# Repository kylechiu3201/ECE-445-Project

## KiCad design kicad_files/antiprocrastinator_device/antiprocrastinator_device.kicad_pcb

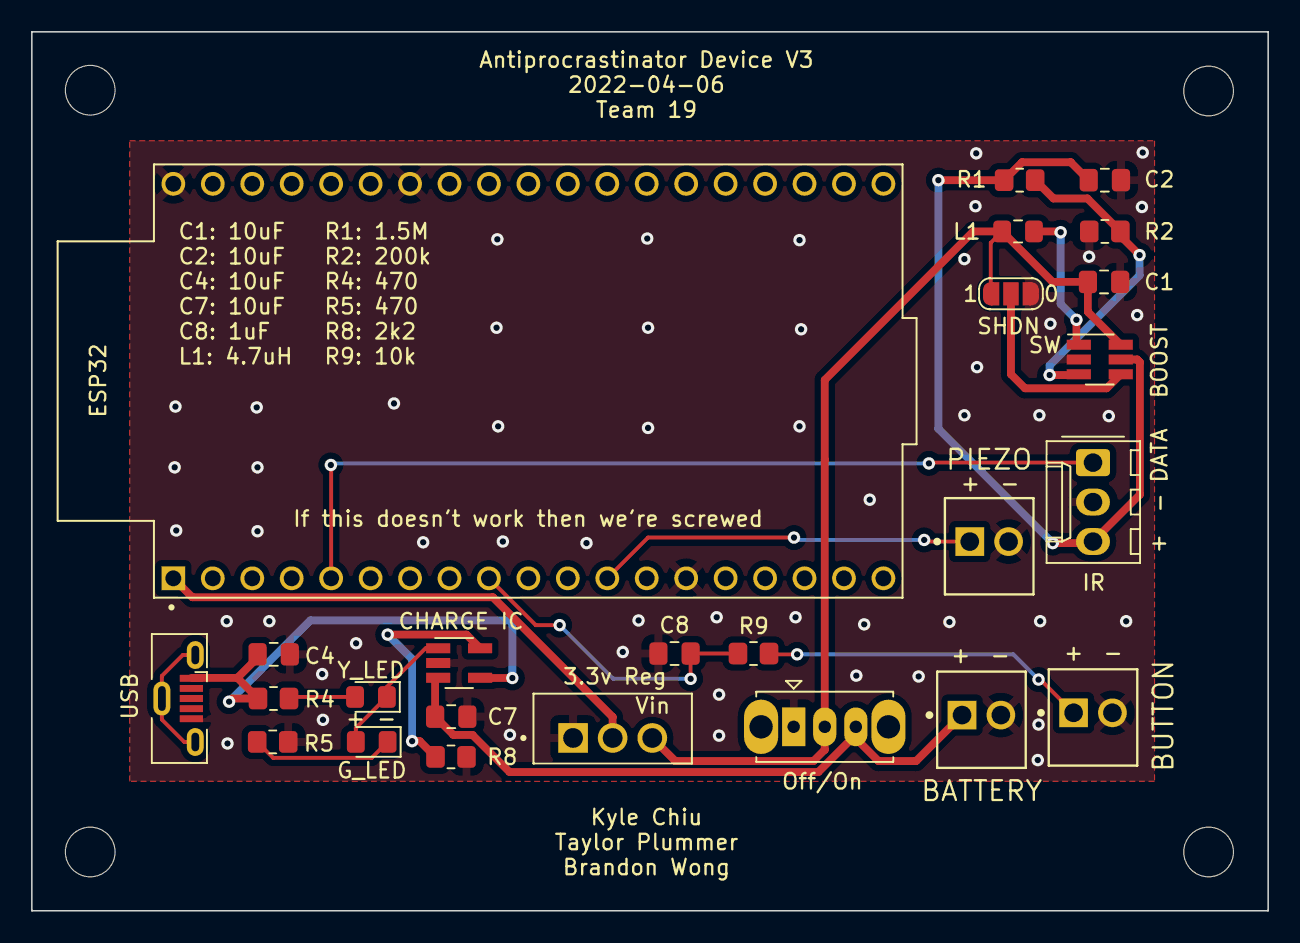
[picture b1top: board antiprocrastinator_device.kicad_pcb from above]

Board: 2 copper layers, 79.6 x 56.6 mm, 29 parts (0 on the bottom side), 17 nets.

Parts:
3.3v Reg: 3.3v-Reg; TO255P1020X450X1968-3
BOOST: Boost Converter; SOT-23-6_Handsoldering
C1, C2, C4, C7: 10uF; C_0805_2012Metric_Pad1.18x1.45mm_HandSolder
C8: 1uF; C_0805_2012Metric_Pad1.18x1.45mm_HandSolder
CHARGE IC: BATT_IC; SOT-23-5_HandSoldering
D2: Y_LED; LED_0805_2012Metric_Pad1.15x1.40mm_HandSolder
D3: G_LED; LED_0805_2012Metric_Pad1.15x1.40mm_HandSolder
ESP32: ESP32; MODULE_ESP32-DEVKITC-32U
H1, H2, H3, H4: MountingHole; MountingHole_3.2mm_M3
J5: PIEZO; Molex-22-04-1021-MFG
J6: BATTERY; Molex-22-04-1021-MFG
J7: BUTTON; Molex-22-04-1021-MFG
J9: IR; Molex_KK-254_AE-6410-03A_1x03_P2.54mm_Vertical
L1: 4.7uH; L_0805_2012Metric_Pad1.15x1.40mm_HandSolder
Off/On: SW_SPDT; SW_Slide_1P2T_CK_OS102011MS2Q
R1: 1.5M; R_0805_2012Metric_Pad1.20x1.40mm_HandSolder
R2: 200k; R_0805_2012Metric_Pad1.20x1.40mm_HandSolder
R4, R5: 470R; R_0805_2012Metric_Pad1.20x1.40mm_HandSolder
R8: 2K2; R_0805_2012Metric_Pad1.20x1.40mm_HandSolder
R9: 10k; R_0805_2012Metric_Pad1.20x1.40mm_HandSolder
SHDN: SolderJumper_3_Open; SolderJumper-3_P1.3mm_Open_RoundedPad1.0x1.5mm_NumberLabels
USB: USB_B_Micro; USB_Micro-B_Molex-105133-0001

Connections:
+3V3: 3.3v Reg.2 (VOUT), ESP32.1 (3V3)
/BATT_OUT: 3.3v Reg.3 (VIN), BOOST.6 (VIN), C1.1, L1.1, Off/On.2 (B), SHDN.1 (A)
/BOOST_FB: BOOST.3 (FB), R1.2, R2.1
/BOOST_SHDN: BOOST.4 (~SHDN), SHDN.2 (C)
/BOOST_SW: BOOST.1 (SW), L1.2
/BOOST_VOUT: BOOST.5 (VOUT), C2.1, J9.3, R1.1
/BUTTON: C8.1, ESP32.9 (IO25), R9.2
/IR_DATA: ESP32.5 (IO34), J9.1
/PIEZO: ESP32.12 (IO14), J5.1
GND: 3.3v Reg.1 (ADJ/GND), BOOST.2 (GND), C1.2, C2.2, C4.2, C7.2, C8.2, CHARGE IC.2 (VSS), ESP32.14 (GND1), ESP32.32 (GND2), ESP32.38 (GND3), J5.2, J6.2, J7.2, J9.2, Off/On.1 (A), R2.2, R5.2, R8.2, SHDN.3 (B), USB.5 (GND)
unnamed: C4.1, CHARGE IC.4 (VDD), R4.1, USB.1 (VBUS)
unnamed: C7.1, CHARGE IC.3 (VBAT), J6.1, Off/On.3 (C)
unnamed: CHARGE IC.1 (STAT), D2.1 (K), D3.2 (A)
unnamed: D2.2 (A), R4.2
unnamed: D3.1 (K), R5.1
unnamed: J7.1, R9.1
unnamed: CHARGE IC.5 (PROG), R8.1

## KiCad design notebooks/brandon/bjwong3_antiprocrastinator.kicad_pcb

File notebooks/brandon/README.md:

## __2/22/2022__
Worked on the first draft of the pcb in KiCad, adding and connecting all the components within the schematic. The piezo buzzer, bluetooth module, and DIP sockets were not within the standard library of footprints and symbols that KiCad provides. For the piezo buzzer, I represented it as a generic buzzer for reference while importing the DIP sockets and bluetooth module from [KiCad Libraries](https://kicad.github.io/footprints/Package_DIP) and [SnapEDA](https://www.snapeda.com/parts/HC-05/ITead%20Studio/view-part/?company=N%2FA&amp;). The schematic is roughly based on the block diagram and will most likely need revisions given more research.

## __2/24/2022__
Finished Design Document. Added more specifics regarding the control subsystem based on TA suggestion. The device will now check for running websites/programs every 5 seconds, and sends the square wave to the buzzer if it detects a blacklisted item. It will run on a 3 minute-interval of sending the signal and not sending the signal should the blacklisted item continue to run.

## __2/28/2022__
Finished the first draft of the pcb board in KiCad. After doing more research on the parts we plan to use as well as importing their models from SnapEDA ([Battery Connector](https://www.snapeda.com/parts/B2B-XH-A(LF)(SN)/JST%20Sales%20America%20Inc./view-part/), [Voltage Regulator](https://www.snapeda.com/parts/LD1117V33/STMicroelectronics/view-part/), [Switch](https://www.snapeda.com/parts/EG1218/E-Switch/view-part/)), I completed a more accurate schematic of what our potentially board will look like. This allowed me to arrange and route the components of the actually PCB edit of the board. The piezo buzzer will most likely have a connector to the board similar to the LED in the soldering assignment. I removed the ISP and microcontroller from the schematic as we are not planning to solder our chip to the board.

## __2/29/2022__
During our PCB board review, we found out that a lot of parts we were planning to use made the project to simple and easy and would require revision to increase the complexity. Will need to figure what aspects of our design need to be changed in order to do so.

## __3/08/2022__
In order to meet requirements, we've adjusted our PCB design to include more functionality and complexity. We added more components and replaced our old bluetooth module and charger. As a result, I rerouted the PCB board based on the new circuit schematic that Kyle made.

## __3/19/2022__
While we are waiting for our parts to come in, I spent some time researching on how to program our ESP32 chip to send and recieve data through bluetooth signals. One website in particular ([Link](https://randomnerdtutorials.com/esp32-bluetooth-classic-arduino-ide/)) has sizeable knowledge on how to achieve this using a smartphone as the device being connected to.

## __3/20/2022__
During our design review, it was brought to our attention that we needed to modify our design to include more hardware complexity, we sat down and discussed what we should add and came up with including an IR sensor, programming our own bluetooth connection with an ESP32, and our own charging circuit.

## __3/21/2022__
Updated the PCB board arrangement to match Kyle's edit to the schematics and created the new gerber files for second round ordering. Looked into to working out how to take our python code and program it into our ESP32 chip. Seems like we can use Micropython to do so.

## __3/28/2022__
Ordered second round PCB based on the revisions made a few days ago

## __4/5/2022__
More research regarding Micropython coding with the ESP32 led me to sample code that allows connection to a serial bluetooth terminal and the sending/receiving of data between the two devices. The IDE that would have to be used would have to be Thonny Python. To test this however, we would first have to assemble everything on to our PCB in order to program it. ([Link](https://forum.micropython.org/viewtopic.php?t=8645))

## __4/7/2022__
Issues popped up with our 2nd round pcb as some of the parts didn't end up fitting to the board correctly as well as some mechanism not being wired so some adjustments need to be made. We went in as a group to test out some of our parts as they had arrived. Some pins in the ESP32 had specific functionality so we were able to map out the ones that were sufficient for what we needed, mainly a pwm pin for sending a square wave to the buzzer and a potentiometer pin for the IR sensor readings.

## __4/12/2022__
Worked on ESP32 bluetooth. Managed to get a connection to my PC and send data both ways. I was able to monitor the connection through Arduino IDE(instead of Thonny) and a bluetooth serial terminal.

## __4/14/2022__
We received our 3rd PCB order only for it to be someone else's PCB, therefore being unusable to us and leading to us getting delayed as we wait for another PCB order.

## __4/18/2022__
Started looking into data transmission using Pybluez, had difficulties with installing the correct packages due to my outdated laptop but eventually I was able to get it working. Will focus more on actually trying to code it later.

## __4/19/2022__
Made progress sending data from a python script to the ESP32 using Pybluez and Pyserial, incorporated that in to the application detection software so that it can send signals to the chip whenever it detects a blakclisted site. Still need to work on hardware side due to pcb difficulties, incorporating the analog sensors with the software detection and chip.

## __4/20/2022__
Worked on starter code to incorporate the bluetooth application detection with the analog sensors by adding on to our initial ESP32 code meant for Arduino IDE. Not sure if it entirely works yet though as we still have yet to assemble everything. We are planning to meet up Thursday to work on it, so hopefully we will get everything ready in time before the mock presentation.

## __4/21/2022__
Went in as a group to work on soldering the parts on to the pcb as it arrived today. Managed to program the chip to work with the IR sensor and buzzer along with detecting both websites and applications so the majority of our project's functionality is working as intended just in time for the mock demo. We still need to update our design document and work on getting our pcb into its enclosure. Other than that, everything is pretty much finalized.

## __4/22/2022__
After the mock demo, We spent the time to pick up more parts and modified our enclosure to fit our pcb. We screwed everything and after a few adjustments to the code, we pretty much have the finalized device. There were some issues with the IR values being inconsistent after soldering to the pcb, so we adjusted the thresholds to have it function accordingly.

## __4/23/2022__
Took some measurements for verification by measuring the decibel value of the piezo buzzer when it goes off. It follows within our requirements so there isn't really a need to change what we have so far.

## __4/24/2022__
Updated our RV tables as it didn't include the added feature of the IR sensor and replaced the ATTiny with the ESP32. Prepping in general for the upcoming demo, figuring out what to say and what points need to be brought up

## __4/25/2022__
Worked on starter slides to incorporate into our mock presentation. Picked out what points were considered important and who was elaborating on each part. Will surely need to edit in the future after getting feedback.

## __5/1/2022__
After feedback from the mock presentation, we redid our slides to incorporate the grainger engineering presentation theme and improved them to be less wordy and more clear to understand. Drew up a few flowcharts regarding the behaviour of the ESP32 code used for the presentation and final paper.

## __5/2/2022__
Did final presentation today. Got through all the talking points smoothly enough with little difficulties. Now all that's really left is the final paper.

## __5/4/2022__
Sat down with the team to write up the paper. I mainly contributed in writing the conclusion(Accomplishments, Uncertainties, Ethical Considerations, Future Work) and abstract section of the paper.

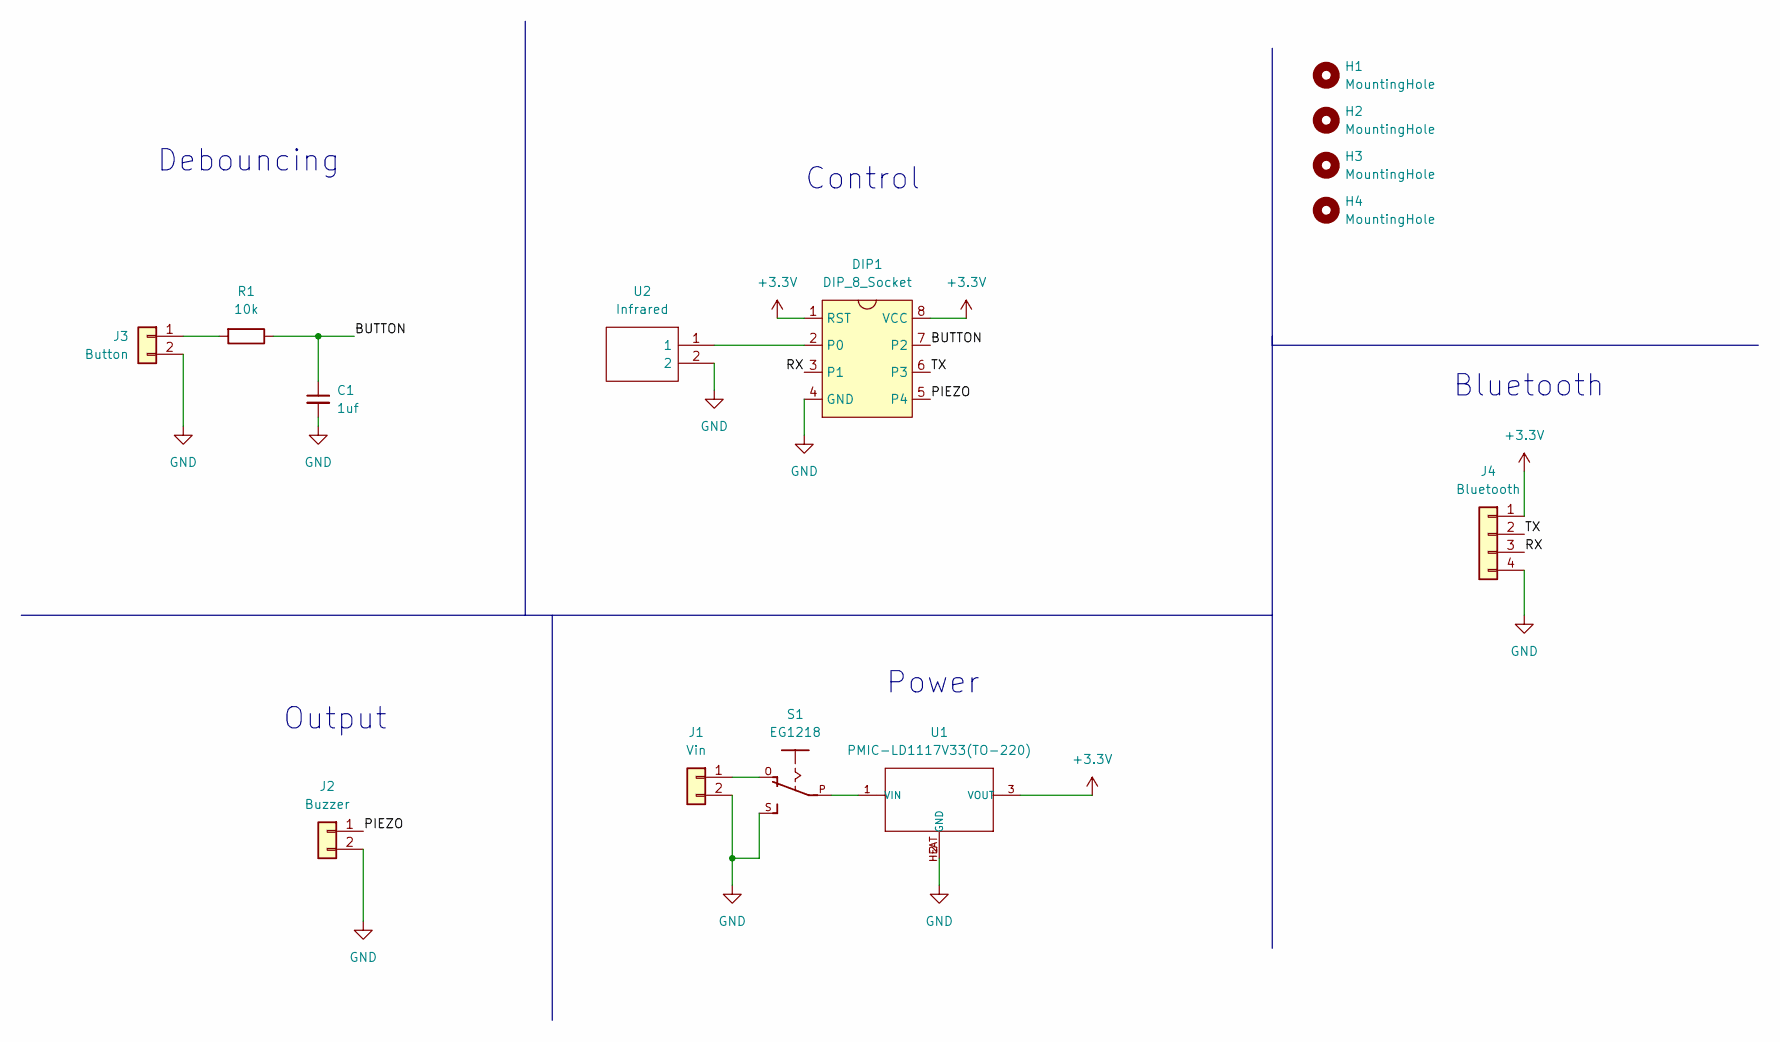
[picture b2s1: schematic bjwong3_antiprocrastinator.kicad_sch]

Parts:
C1: 1uf; C_0805_2012Metric_Pad1.18x1.45mm_HandSolder
DIP1: DIP_8_Socket; DIP-8_W7.62mm_Socket
H1, H2, H3, H4: MountingHole; MountingHole_3.2mm_M3
J1: Vin; Molex_KK-254_AE-6410-02A_1x02_P2.54mm_Vertical
J2: Buzzer; Molex_KK-254_AE-6410-02A_1x02_P2.54mm_Vertical
J3: Button; Molex_KK-254_AE-6410-02A_1x02_P2.54mm_Vertical
J4: Bluetooth; Molex_KK-254_AE-6410-04A_1x04_P2.54mm_Vertical
R1: 10k; R_0805_2012Metric_Pad1.20x1.40mm_HandSolder
S1: EG1218
U1: PMIC-LD1117V33(TO-220); TO-220; MPN LD1117V33
U2: Infrared; GP2Y0A21YK0F; Manufacturer_Part_Number GP2Y0A21YK0F; Mouser Part Number 852-GP2Y0A21YK0F

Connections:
+3V3: DIP1.1 (RST), DIP1.8 (VCC), J4.1, U1.3 (VOUT)
/BUTTON: C1.1, DIP1.7 (P2), R1.1
/PIEZO: DIP1.5 (P4), J2.1
/RX: DIP1.3 (P1), J4.3
/TX: DIP1.6 (P3), J4.2
GND: C1.2, DIP1.4 (GND), J1.2, J2.2, J3.2, J4.4, S1.S, U1.2 (GND), U1.HEAT (GND), U2.2
unnamed: DIP1.2 (P0), U2.1
unnamed: J3.1, R1.2
unnamed: J1.1, S1.O
unnamed: S1.P, U1.1 (VIN)

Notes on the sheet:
Bluetooth
Power
Debouncing
Output
Control

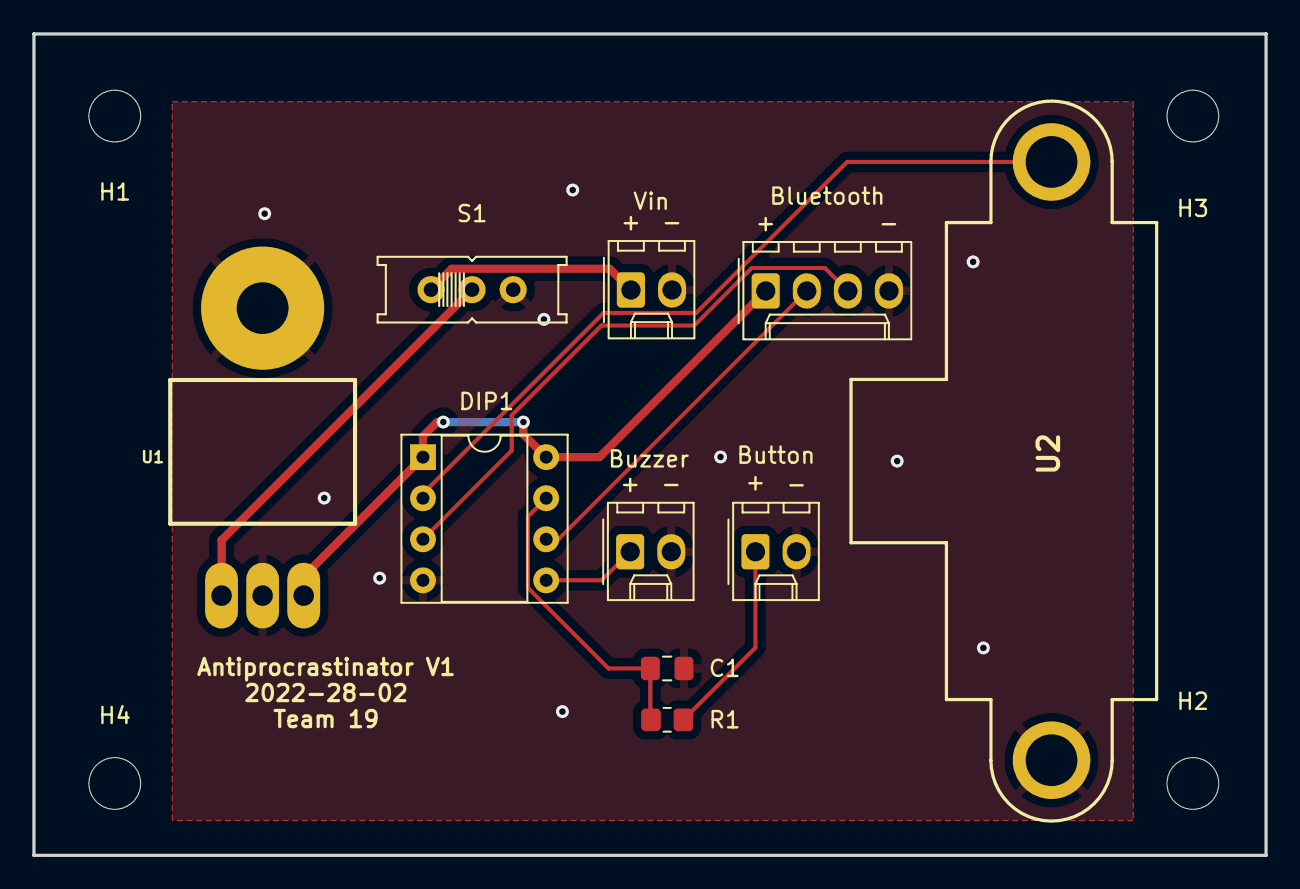
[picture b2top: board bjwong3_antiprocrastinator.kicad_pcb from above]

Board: 2 copper layers, 76.2 x 50.8 mm, 14 parts (0 on the bottom side), 10 nets.

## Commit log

2022-05-31 copy ECE 445 folder to repo
